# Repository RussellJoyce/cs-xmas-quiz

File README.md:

cs-xmas-quiz
============

Computer Science Christmas Quiz system

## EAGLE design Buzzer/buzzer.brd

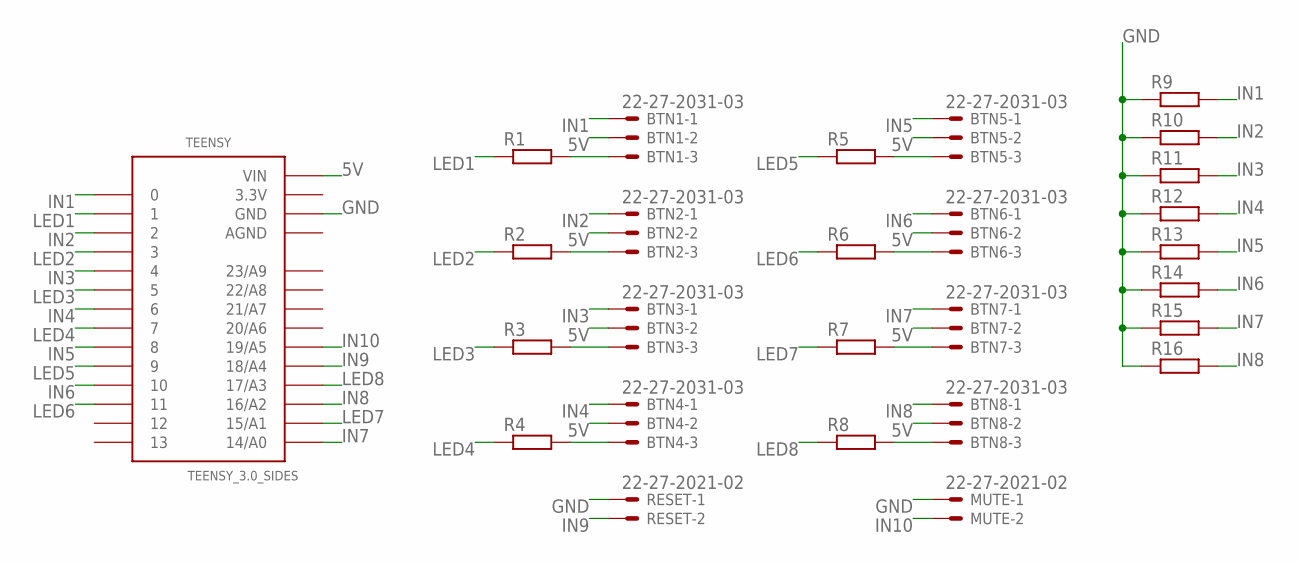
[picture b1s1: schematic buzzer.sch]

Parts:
BTN1, BTN2, BTN3, BTN4, BTN5, BTN6, BTN7, BTN8: 22-27-2031-03; 6410-03
MUTE: 22-27-2021-02; 6410-02
R1, R2, R3, R4, R5, R6, R7, R8, R9, R10, R11, R12, R13, R14, R15, R16: R0207/10; 0207/10
RESET: 22-27-2021-02; 6410-02
TEENSY: TEENSY_3.0_SIDES

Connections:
3.3V: TEENSY.3.3V
5V: BTN1.2, BTN2.2, BTN3.2, BTN4.2, BTN5.2, BTN6.2, BTN7.2, BTN8.2, TEENSY.VIN
AGND: TEENSY.AGND
GND: MUTE.1, R9.1, R10.1, R11.1, R12.1, R13.1, R14.1, R15.1, R16.1, RESET.1, TEENSY.GND
IN1: BTN1.1, R9.2, TEENSY.0
IN2: BTN2.1, R10.2, TEENSY.2
IN3: BTN3.1, R11.2, TEENSY.4
IN4: BTN4.1, R12.2, TEENSY.6
IN5: BTN5.1, R13.2, TEENSY.8
IN6: BTN6.1, R14.2, TEENSY.10
IN7: BTN7.1, R15.2, TEENSY.14/A0
IN8: BTN8.1, R16.2, TEENSY.16/A2
IN9: RESET.2, TEENSY.18/A4
IN10: MUTE.2, TEENSY.19/A5
LED1: R1.1, TEENSY.1
LED2: R2.1, TEENSY.3
LED3: R3.1, TEENSY.5
LED4: R4.1, TEENSY.7
LED5: R5.1, TEENSY.9
LED6: R6.1, TEENSY.11
LED7: R7.1, TEENSY.15/A1
LED8: R8.1, TEENSY.17/A3
unnamed: BTN1.3, R1.2
unnamed: BTN4.3, R4.2
unnamed: BTN5.3, R5.2
unnamed: BTN7.3, R7.2
unnamed: BTN8.3, R8.2
unnamed: BTN2.3, R2.2
unnamed: BTN3.3, R3.2
unnamed: BTN6.3, R6.2

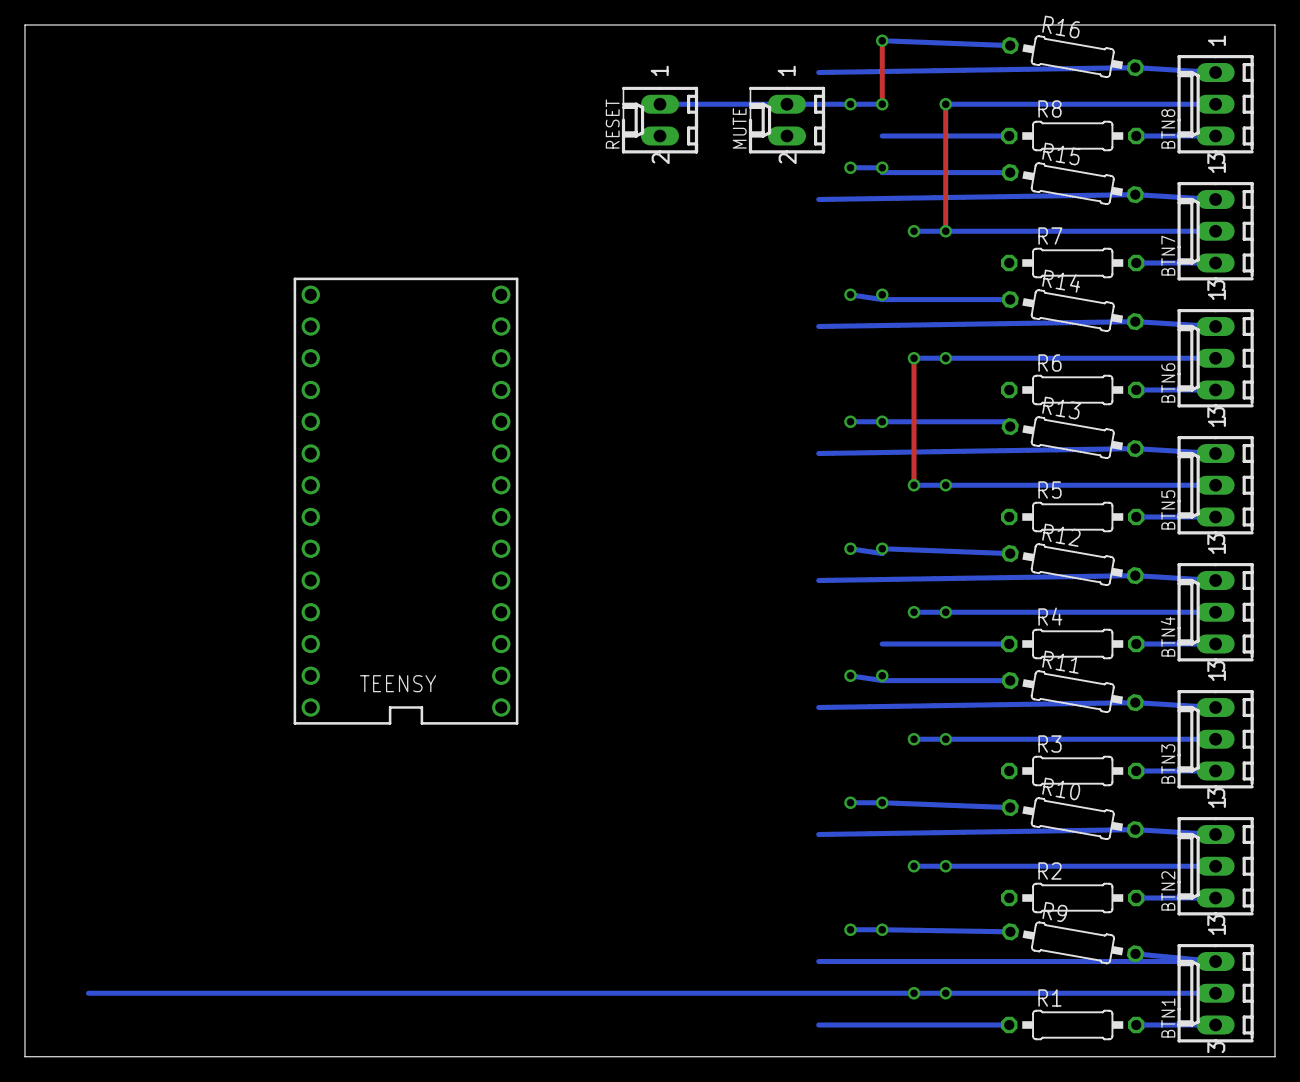
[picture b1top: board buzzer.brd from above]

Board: 2 copper layers, 100.0 x 82.5 mm, 27 parts (0 on the bottom side), 28 nets.

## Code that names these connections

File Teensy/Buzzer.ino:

/* Quiz Buzzer System
   Teensy 3.1 becomes a USB game controller with ten buttons, plus a serial device

   You must select 'Quiz Buzzer System' from the "Tools > USB Type" menu
   (Copy 'hardware' folder into Arduino installation folder to overwrite default Teensy types)
*/

#define BTN1  0
#define BTN2  1
#define BTN3  2
#define BTN4  3
#define BTN5  4
#define BTN6  5
#define BTN7  6
#define BTN8  7
#define BTN9  8
#define BTN10 9
#define LED1 10
#define LED2 11
#define LED3 12
#define LED4 14
#define LED5 15
#define LED6 16
#define LED7 17
#define LED8 18
#define LEDB 13

boolean led = false;

boolean buttons[10];
boolean reset = false;

void setup() {
  // Set up button/LED pins
  pinMode(BTN1, INPUT);
  pinMode(BTN2, INPUT);
  pinMode(BTN3, INPUT);
  pinMode(BTN4, INPUT);
  pinMode(BTN5, INPUT);
  pinMode(BTN6, INPUT);
  pinMode(BTN7, INPUT);
  pinMode(BTN8, INPUT);
  pinMode(BTN9, INPUT_PULLUP);
  pinMode(BTN10, INPUT_PULLUP);
  pinMode(LED1, OUTPUT);
  pinMode(LED2, OUTPUT);
  pinMode(LED3, OUTPUT);
  pinMode(LED4, OUTPUT);
  pinMode(LED5, OUTPUT);
  pinMode(LED6, OUTPUT);
  pinMode(LED7, OUTPUT);
  pinMode(LED8, OUTPUT);
  pinMode(LEDB, OUTPUT);

  // Set up serial
  Serial.begin(115200);

  // Make game controller use manual event sending
  Quiz.useManualSend(true);
}

void loop() {
  buttons[0] = digitalRead(BTN1);
  buttons[1] = digitalRead(BTN2);
  buttons[2] = digitalRead(BTN3);
  buttons[3] = digitalRead(BTN4);
  buttons[4] = digitalRead(BTN5);
  buttons[5] = digitalRead(BTN6);
  buttons[6] = digitalRead(BTN7);
  buttons[7] = digitalRead(BTN8);
  buttons[8] = digitalRead(BTN9);
  buttons[9] = digitalRead(BTN10);

  Quiz.button(1, buttons[0]);
  Quiz.button(2, buttons[1]);
  Quiz.button(3, buttons[2]);
  Quiz.button(4, buttons[3]);
  Quiz.button(5, buttons[4]);
  Quiz.button(6, buttons[5]);
  Quiz.button(7, buttons[6]);
  Quiz.button(8, buttons[7]);
  Quiz.button(9, buttons[8]);
  Quiz.button(10, buttons[9]);
  Quiz.send_now();

  reset = digitalRead(23);

  buttonsPersistent[0] = buttons[0] || (buttonsPersistent[0] && !reset);

  digitalWrite(10, !buttonsPersistent[0]);
  // digitalWrite(11, !digitalRead(1));
  // digitalWrite(12, !digitalRead(2));

  //Serial.println("Hello!");

  led = !led;
  digitalWrite(LEDB, led);

  delay(100);
}

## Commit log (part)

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2019-12-03 Plumb in connections to Numbers view
2019-12-03 Numbers uses the same view on the tablets as Text
2019-12-03 Numbers round version 1
2019-12-03 Added basics of music round
2019-12-03 Update display of Geography round
2019-12-03 Set Higher/Lower back to True/False
2019-12-03 Add Numbers mode to web. Also (sorry), fix geography clickthrough issue
2019-12-03 Changed higher/lower back to true/false
2019-12-03 Clamp the output of the geography click
2019-12-03 Added record scratch sounds as music round buzz noises
2019-12-03 Pause music round music when resetting round (useful when changing view)
2019-12-03 Removed hidden files from music round listing
2019-12-03 Added basic LEDs animation while music is playing in music round
    This could do with testing, before making more interesting and musical.
2019-12-04 Removed one of the music buzz scratch sounds
2019-12-04 Disabled music round buzzers between reset and play actions
2019-12-04 Added playground for testing music round visualisations
2019-12-05 Made a copy of Teensy Buzzer code for use from now on
2019-12-05 Removed physical quiz buzzer buttons/LEDs code from Teensy QuizBox
2019-12-05 Add validation for Numbers mode
2019-12-05 Fixed yo' number shizzle
    It's number, idiot.
2019-12-05 Reset all elements of the Numbers view on Reset Round
2019-12-05 Removed old buzzers HID and LED code from Quiz Server
2019-12-05 Updated nodehun node module version so it compiles ok
2019-12-05 Fixed LEDs turning off as soon as app finishes launching
    Music initialisation was overriding idle view animation
2019-12-06 Updated node WS module code to work with v3.0+
2019-12-06 Made LEDs serial port automatically reconnect every 5 seconds when lost
2019-12-06 Fixed flickering at the end of pointless/pulse LED animations
    This one's been annoying me for years
2019-12-06 Moved Teensy serial code to the main loop instead of being on a timer
    This should make things more reliable now and remove some race
    conditions, given we no longer have to prioritise buzzer presses in the
    Teensy code. This currently has the side effect of queueing certain
    animations in the serial buffer, however, potentially leading to long
    chains of animations with no way to interrupt them. Ideally all the
    animations would be asynchronous (see Megamas), but we can dream...
2019-12-06 Removed hacky delays in serial code, given we now handle serial sensibly
    Hopefully this won't cause issues now that serial is handled by the main
    loop of the Teensy code. I believe these were just in here to begin with
    as a last-minute hack to reduce the effects/likelihood of serial
    handling race conditions.
2019-12-06 Added message to controller window title when serial port is reconnecting
2019-12-06 Removed unused Node modules
    Left over after all the excitement of Boggle.
2019-12-06 Updated some LED command definitions
2019-12-06 Added music peak levels on LEDs during music round playback
    And it actually really works!
2019-12-09 Modified visualisation power function for music round
    Also some tweaks to the music testing Playground
2019-12-09 Updated ORSSerialPort to v2.1.0 (closes #21)
2019-12-09 Reduced brightness of idle Pointless LEDs
2019-12-09 Changed Teensy code for setting LEDs colour to match definition in Swift
    I.e. set colour from a list of colours, rather than from team colours
2019-12-09 Ignore music files that haven't been explicitly checked in to the repo
2019-12-09 Make true/false view timer LEDs look nicer
    They'll show dim when reset, then get brighter on the first beep (5 secs)
2019-12-09 Add a bit of LEDs twinkle to the otherwise LED-dull geography round
    We could probably do with a few more animations
2019-12-09 Removed geography round test guesses
2019-12-09 Ensure UI elements are reset when switching rounds
2019-12-09 Added fireworks for anniversary
2019-12-09 Added "tenth anniversary" badge to idle view
2019-12-09 Moved fireworks into the sky
    Let's see what Ian thinks...
2019-12-09 Decreased likelihood of random buzzer sound
2019-12-09 Made LED twinkle animation more twinkly
2019-12-09 Made transition between LED animations smoother
    Removed resetting animations when unnecessary, and removed assumption
    that a round reset always wants to clear LEDs.
2019-12-10 Make text scene show the number of points scored
2021-11-21 Remove anniversary stuff, tweaks to layout
2021-11-21 Implement Buzzcocks mode
2021-11-21 Ignore geography files
2021-11-21 Remove trailing geography image
2021-11-21 Fix some deprecations and safety warnings
2021-11-22 Remove lodash dep
2022-11-30 Add mode to prevent buzzer queuing
2022-11-30 Update example geography images
2022-11-30 Add DNS server to nodeserver
2022-11-30 Update scoring to give points to anyone in the top half
2022-11-30 Particle effects for winners
2022-12-01 Add switch for alternate buzzers (default off)
2022-12-04 Update to personal domain
2022-12-05 Tweak true/false client pages
2022-12-06 Remove bodyScrollLock and add a viewport meta tag. Seems to all be fixed on iOS at least.
2022-12-06 Update with new round capabilities
2022-12-06 Make timer LEDs reflect different start times
2023-11-06 Add unique mode
2023-11-06 Adding unique mode
2023-11-23 Add a message if team is taken
2023-11-23 Remove old game views
2023-11-25 Support for LEDs on a websocket via ESP32
2023-11-25 Remove 10 team limit in client
2023-11-25 Clean up git index
2023-11-25 Update ignores
2023-11-25 Add quizleds creds to ignore
2023-11-26 Support for more teams
2023-11-26 Tidy up
2023-11-26 Text/Numbers support more teams
2023-11-26 The airhorn was really quite unpleasant
2023-12-01 Fix some buzz animations, update led pin to pin13
2023-12-01 Make text answers scrollable
2023-12-01 Different method of calculating time offset
2023-12-07 Add quieter buzzer sound and option
2023-12-08 Added counter animation
2023-12-08 Fix pulses
2023-12-08 Added minute timer to the Timer scene
2023-12-10 Remove old tests
2023-12-10 Use updated subnet
2023-12-10 Tweak behaviour of test buttons
2023-12-10 Disable attempting to open Quiz Leds serial port
2023-12-10 Tweak some minor scoring bugs
2023-12-10 Stop music at end of timer
2023-12-10 Fix team colour bug in buzz animations. Add new buzz animation
2023-12-10 Update buzzer scene design
2023-12-10 Add snow to buzzers
2023-12-10 Make counter opacity 0
2023-12-11 Fix crash when team > 10 buzzes on Idle Scene
2023-12-11 Timer doesn't need to pulse the SpriteKit scene as well as the LEDs and music
2023-12-11 Make team already taken message red
2023-12-15 True/False tweaks and fixes
2023-12-15 Remove the QuizViewController and associated indirection now that all scenes are SpriteKitScenes
2023-12-15 Remove serial port and all serial references
2023-12-16 Remove submodules, add Starscream and SwiftyJson as Swift Package Manager deps. New Starscream has a pile of breaking changes that needed handling.
2023-12-16 Remove unnecessary indirection
2023-12-16 Bug with reading the wrong file on startup
2023-12-16 Minor restructure
2023-12-16 Update current year
2024-11-04 Add Scores scene and assocated assets
2024-11-08 Add ranking into Scores, and textual output
2024-11-30 Change domain and update certs
2024-11-30 Update geography graphics for more teams, and add LED feedback to guesses
2024-12-01 Make scoring more generous
2024-12-01 Pass through a debug mode toggle
2024-12-01 Remove the option of team 15 because you can't be trusted
2024-12-01 Bugfix, Pass into LED anim the team ID, not position
2024-12-01 Make scores all visible on the controller window
2024-12-01 Add dramatic sounds to scoreboard
2024-12-03 Prevent crash if trying to show zero guesses
2024-12-03 Add toggle for buzzer sounds
2025-01-03 Add video player
2025-10-24 Update some labels for Video files
2025-10-24 Tidy up some constraints for new macOS
2025-10-24 Remove unused plist
2025-10-24 Refinements to buzzer scene animations
2025-10-24 Fancy swoosh animation on buzzernodes
2025-10-24 Additional animations on score
2025-10-24 Fix bug preventing switch back to music mode after playing a video
2025-10-24 Darken shadow
2025-10-24 General tidy up and refactor
2025-10-24 Remove ClockNode
2025-10-24 fetch script +x flag
2025-10-24 Added timestamping of client connections, status lights on the UI, and an API to query
2025-10-25 Added snow effect (definitely a bad idea...)
2025-10-25 Periodically poll the server for list of clients
2025-10-25 Support for higher/lower to report back to the client what was selected
2025-10-25 Make T/F fancier, some refactoring
2025-10-25 Sounds fixed in T/F
2025-10-25 Refactoring and tidying up
2025-10-25 Entrance shimmer on TeamNode added as constructor parameter
2025-10-26 You can organise the project browser apparently
2025-10-26 Overhaul of windowing mode, allows for entering and exiting fullscreen
2025-10-26 Some logic errors with test buzzers
2025-10-26 EIGHT
2025-10-28 New idle screen with lots of new graphics
2025-10-28 Yeah the snow animation used ~75x the power...
2025-10-28 Feedback for when non-numbers are entered into the numbers mode
2025-10-31 Slight updates to idle
2025-10-31 Allow toggle between True/False and Higher/Lower
2025-11-01 Add sound toggle for T/F, significant restructure of some code
2025-11-01 Small refactor
2025-11-01 Skip MainMenu nib if not holding cmd
2025-11-01 Use sendIfConnected
2025-11-02 Add test facility to the idle screen
2025-11-05 Change timing logic so that it doesnt count when not foreground
2025-11-06 Snow optimisation using simulation advance
2025-11-08 Better font
2025-11-14 The grand revival of Pointless!
2025-11-14 Pointless improvements and sounds
2025-11-15 Update for pointless
2025-11-15 Tweak for testing
2025-11-15 Start work on adding VU meters
2025-11-15 More pointless refinements
2025-11-15 Trim out meters for the moment
2025-11-15 Fix some filter nonsense
2025-11-15 Use MARK comments - they are rad
2025-11-15 Move extensions into one place
2025-11-17 Introduce a QuizRound protcol to tidy up some logic
2025-11-17 Fix idiot bug
2025-11-19 Fix library adjustments so that we now build again
2025-11-19 xcode update adjusts some IB nibs
2025-11-19 Add support for faster team colour pulses, and a new twinkle animation
2025-11-19 Add LED animations throughout new scenes
2025-11-19 Support to set the target colour of animations
2025-11-19 Support team target colour, and tidy LED calls
2025-11-27 Fix regression on video player
2025-11-28 Update to support multiple SSIDs
2025-11-28 Fix regression in geo
2025-11-28 Add descending mode to pointless
2025-11-28 Hardening
2025-11-28 Tweaks to LEDs on Music round
2025-11-28 Move some questions out of VC
2025-11-28 Layout adjustments
2025-11-28 Fix some potential out of bounds crashes
2025-11-28 Allow repeated text submissions
2025-12-01 Fix small bug with numbers to emoji
2025-12-01 Fix a few small things
2025-12-01 Update to support multiple SSIDs and some LED string testing features
2025-12-03 Fix regression to show updates to the controller every Text entry
2026-02-15 Add offline mode
2026-02-15 remove starscream and replace with native swift websockets
2026-02-24 Add test harness, with additional ws (not wss) endpoint
2026-02-24 Xcode screwing around
2026-02-26 Break buzzer effects out and add more
2026-02-26 Move questions into a Questions dir
2026-02-26 Ignore questions
2026-02-26 Files moved
2026-02-26 Clean old files
